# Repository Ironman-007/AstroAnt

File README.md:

# AstroAnt
Phase II of Rovables

The AstroAnt is the second generation of the Rovable project. The AstroAant also use magnetic wheels to attach to magnetic surface.

The AstroAnt is a modular design, and can carry different sensors to finish different kinds of diognostic missions, such as finding abnormal heating source, check CO2 leakage, detect metal flaw, and streaming video from remote.

Files descriptions:

- The 3D model of the robot is in the [Small_magnets_R821_with_gearbox](3dmodel/Small_magnets_R821_with_gearbox).

- The firmware of the robot is in [AstroAnt](Software/AstroAnt).

- The PC program (UI) is the [gui.py](Software/GUI_python/gui.py). Open with command line: ```python3 gui.py```

- The PCB design is in the [PCB](PCB). The [mainboard_v1](PCB/Mainboard/mainboard_v1/) is the design of the main control board, developed with KiCAD. The others are sensor modules design.

- The software of the central station for collecting data and distributing command is in [central_station](Software/Central_station/central_station/).

- The software of the central station for Camera in [cam_central](Software/Central_station/cam_central/).

- The Box design for the Zero-G flight test is in [Ant_Test_Box_DEC](3dmodel/Ant_Box_DEC/).

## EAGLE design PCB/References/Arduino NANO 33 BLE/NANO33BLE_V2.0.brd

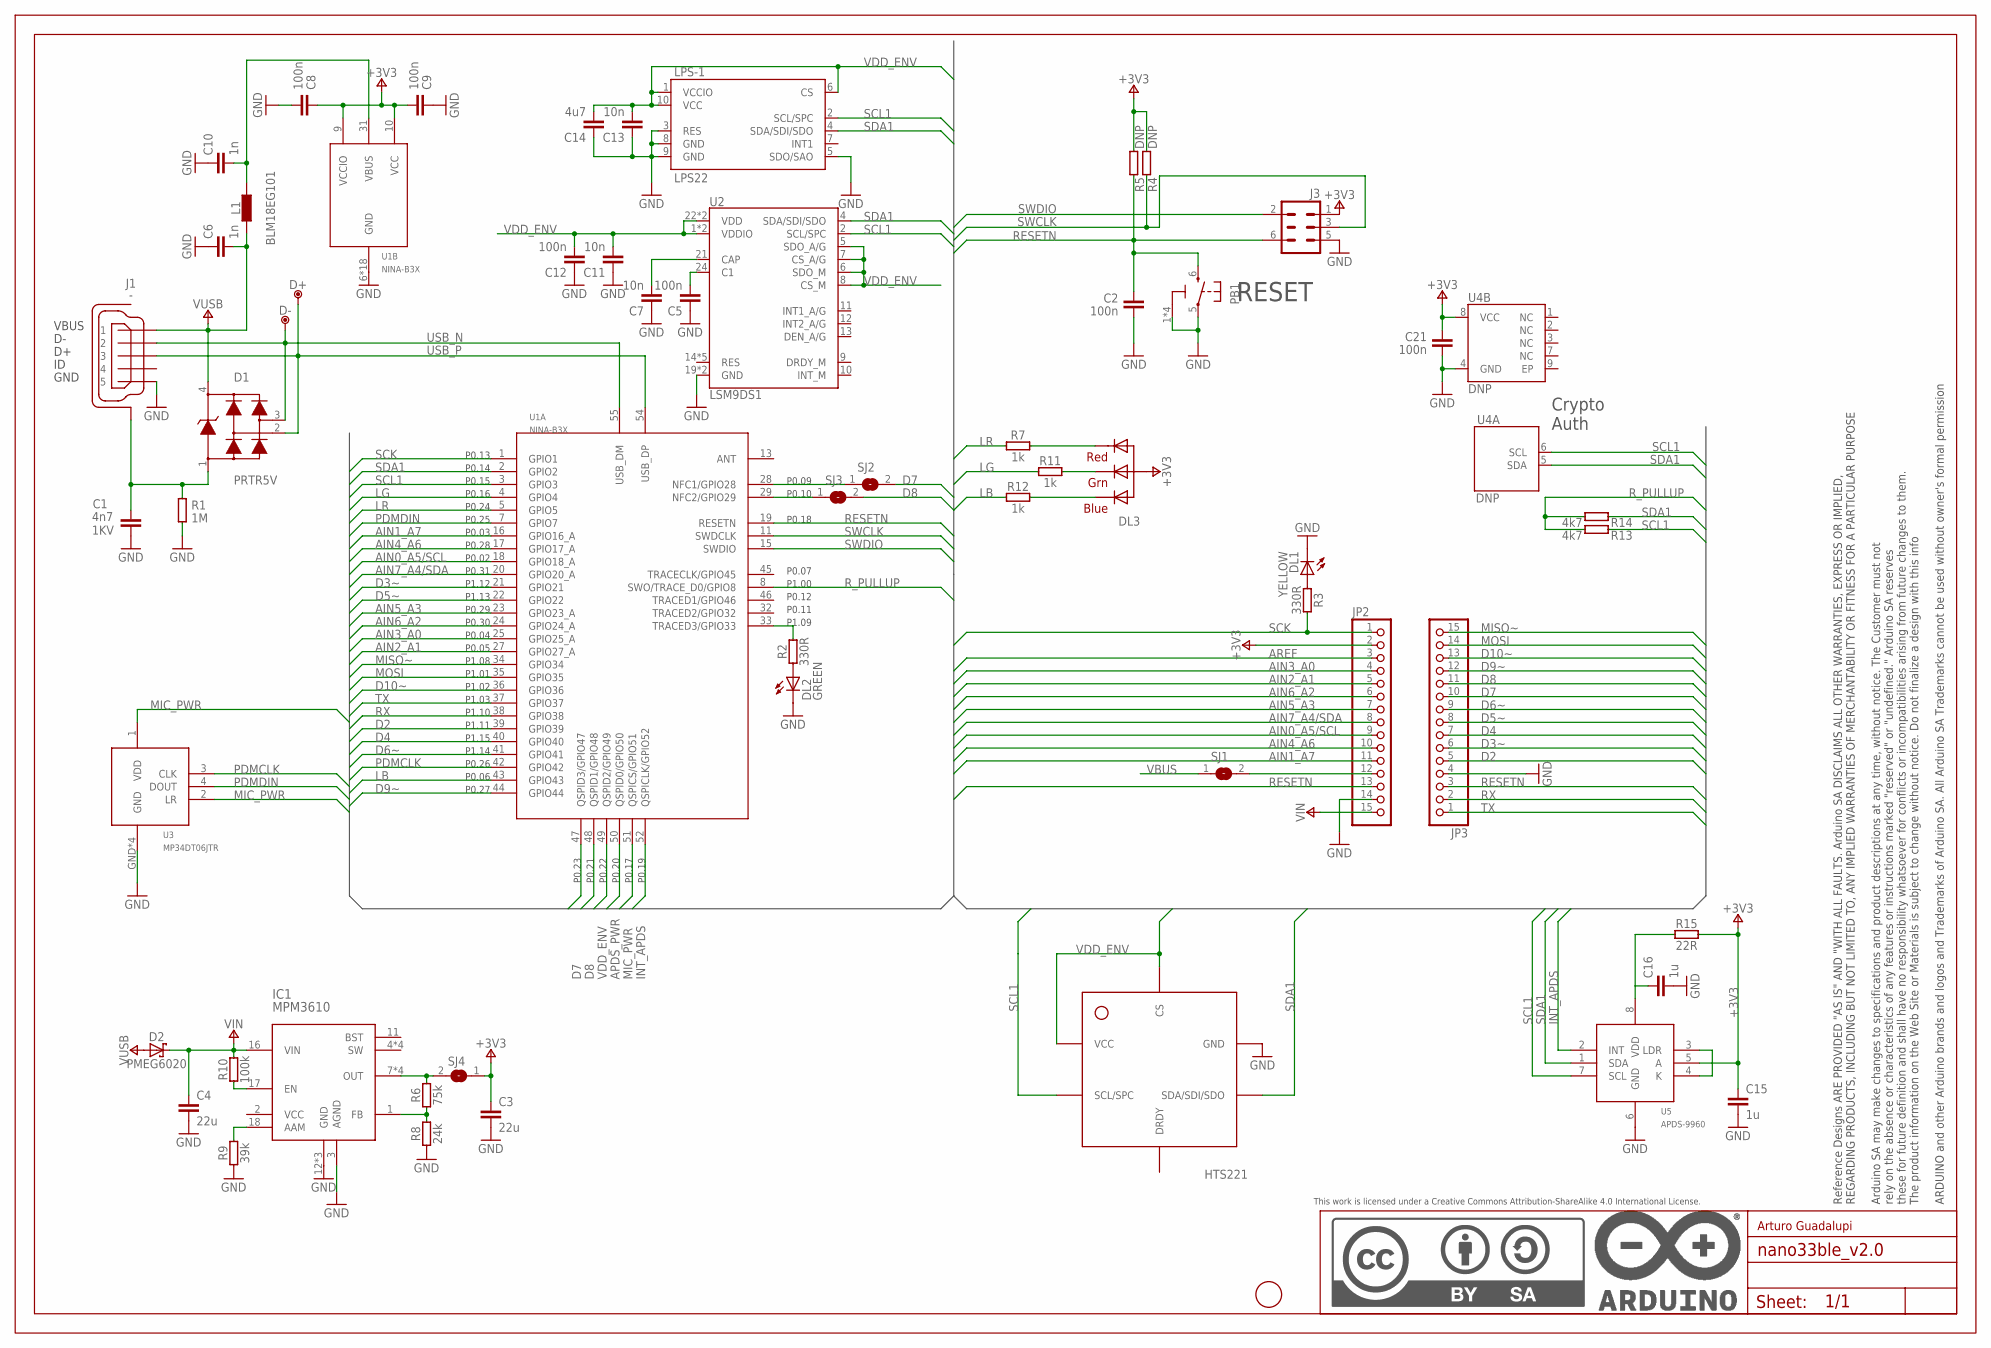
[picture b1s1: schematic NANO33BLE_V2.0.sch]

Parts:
C1: 4n7; 0805-R2013X50N; VOLTAGE 1KV
C2, C5, C8, C9, C12, C21: 100n; 0402-1005X55N
C3, C4: 22u; 0805-R2013X50N
C6, C10: 1n; 0402-1005X55N
C7, C11, C13: 10n; 0402-1005X55N
C14: 4u7; 0402-1005X55N
C15, C16: 1u; 0402-1005X55N
D1: PRTR5V; SOT190P230X110-4N
D2: PMEG6020; SODFL3517X110N
D+: DNP; TP-1.00MM
D-: DNP; TP-1.00MM
DL1: YELLOW; LEDC1608X80N-AK
DL2: GREEN; LEDC1608X80N-AK
DL3: -; SMLP34RGB2W
FD1: DNP; FD-1-1.5
FRAME1: DNP; FRAME
HS-1: HTS221
IC1: MPM3610
J1: -; ZX62-AB-5PA
J3: DNP; 2X03-TP1
JP2, JP3: PINHD-1X15-CASTELLATED; 1X15-CASTELL
L1: BLM18EG101; 0603-1608X90N
LPS-1: LPS22; LPS22H
PB1: PTS820; C&K_PTS820_NO_HOLES
R1: 1M; 0402-1005X55N
R2, R3: 330R; 0402-1005X55N
R4, R5: DNP; 0402-1005X55N
R6: 75k; 0402-1005X55N
R7, R11, R12: 1k; 0402-1005X55N
R8: 24k; 0402-1005X55N
R9: 39k; 0402-1005X55N
R10: 100k; 0402-1005X55N
R13, R14: 4k7; 0402-1005X55N
R15: 22R; 0402-1005X55N
SJ1, SJ2, SJ3, SJ4: DNP; SJ
U1: NINA-B3X
U2: LSM9DS1; LSM9DS1_TEMP_LGA24-8X4
U3: MP34DT06JTR; HCLGA
U4: DNP; SON50P300X200X60-9N-EP160X140
U5: APDS-9960; APDS9960

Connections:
+3V3: C3.1, C8.1, C9.2, C15.1, C21.1, DL3.1 (A), J3.1, JP2.2, R4.2, R5.2, R15.2, SJ4.1, U1.9 (VCCIO), U1.10 (VCC), U4.8 (VCC), U5.5 (A)
AIN0_A5/SCL: JP2.9, U1.18 (GPIO18_A)
AIN1_A7: JP2.11, U1.16 (GPIO16_A)
AIN2_A1: JP2.5, U1.27 (GPIO27_A)
AIN3_A0: JP2.4, U1.25 (GPIO25_A)
AIN4_A6: JP2.10, U1.17 (GPIO17_A)
AIN5_A3: JP2.7, U1.23 (GPIO23_A)
AIN6_A2: JP2.6, U1.24 (GPIO24_A)
AIN7_A4/SDA: JP2.8, U1.20 (GPIO20_A)
APDS_PWR: U1.50 (QSPID0/GPIO50)
AREF: JP2.3
D2: JP3.5, U1.39 (GPIO39)
D3~: JP3.6, U1.21 (GPIO21)
D4: JP3.7, U1.40 (GPIO40)
D5~: JP3.8, U1.22 (GPIO22)
D6~: JP3.9, U1.41 (GPIO41)
D7: JP3.10, SJ2.2, U1.47 (QSPID3/GPIO47)
D8: JP3.11, SJ3.2, U1.48 (QSPID1/GPIO48)
D9~: JP3.12, U1.44 (GPIO44)
D10~: JP3.13, U1.36 (GPIO36)
GND: C1.2, C2.2, C3.2, C4.2, C5.1, C6.1, C7.1, C8.2, C9.1, C10.1, C11.1, C12.1, C13.1, C14.1, C15.2, C16.2, C21.2, DL1.C, DL2.C, HS-1.P$5.GND (GND), IC1.3 (AGND), IC1.12 (GND), IC1.13 (GND), IC1.14 (GND), J1.5, J3.5, JP2.14, JP3.4, LPS-1.3 (RES), LPS-1.5 (SDO/SAO), LPS-1.8 (GND), LPS-1.9 (GND), PB1.1 (3), PB1.2 (3), PB1.3, PB1.4 (3), PB1.5 (1), R1.1, R8.1, R9.1, U1.6 (GND), U1.12 (GND), U1.14 (GND), U1.26 (GND), U1.30 (GND), U1.53 (GND), U1.GND@1 (GND), U1.GND@2 (GND), U1.GND@3 (GND), U1.GND@4 (GND), U1.GND@5 (GND), U1.GND@6 (GND), U1.GND@7 (GND), U1.GND@8 (GND), U1.GND@9 (GND), U1.GND@10 (GND), U1.GND@11 (GND), U1.GND@12 (GND), U2.19 (GND), U2.20 (GND), U3.GND, U3.GND@2 (GND), U3.GND@3 (GND), U3.GND@4 (GND), U4.4 (GND), U5.6 (GND)
INT_APDS: U1.52 (QSPICLK/GPIO52), U5.2 (INT)
LB: R12.1, U1.43 (GPIO43)
LG: R11.1, U1.4 (GPIO4)
LR: R7.1, U1.5 (GPIO5)
MIC_PWR: U1.51 (QSPICS/GPIO51), U3.1 (VDD), U3.2 (LR)
MISO~: JP3.15, U1.34 (GPIO34)
MOSI: JP3.14, U1.35 (GPIO35)
unnamed: C1.1, D1.1, J1.6 (SH), J1.7 (SH), J1.8 (SH), J1.9 (SH), J1.10 (SH), J1.11 (SH), R1.2
unnamed: DL2.A, R2.1
unnamed: DL1.A, R3.1
unnamed: C5.2, U2.24 (C1)
unnamed: IC1.1 (FB), R6.1, R8.2
unnamed: IC1.18 (AAM), R9.2
unnamed: IC1.17 (EN), R10.1
unnamed: C7.2, U2.21 (CAP)
unnamed: U5.3 (LDR), U5.4 (K)
unnamed: R2.2, U1.33 (TRACED3/GPIO33)
unnamed: DL3.3 (BLUE_C), R12.2
unnamed: DL3.2 (RED_C), R7.2
unnamed: DL3.4 (GREEN_C), R11.2
unnamed: JP2.12, SJ1.2
unnamed: C16.1, R15.1, U5.8 (VDD)
unnamed: IC1.7 (OUT), IC1.8 (OUT), IC1.9 (OUT), IC1.20 (OUT), R6.2, SJ4.2
NFC1: SJ2.1, U1.28 (NFC1/GPIO28)
NFC2: SJ3.1, U1.29 (NFC2/GPIO29)
PDMCLK: U1.42 (GPIO42), U3.3 (CLK)
PDMDIN: U1.7 (GPIO7), U3.4 (DOUT)
RESETN: C2.1, J3.6, JP2.13, JP3.3, PB1.6 (2), R5.1, U1.19 (RESETN)
RX: JP3.2, U1.38 (GPIO38)
R_PULLUP: R13.2, R14.2, U1.8 (SWO/TRACE_D0/GPIO8)
SCK: JP2.1, R3.2, U1.1 (GPIO1)
SCL1: HS-1.P$2.SCL/SPC (SCL/SPC), LPS-1.2 (SCL/SPC), R13.1, U1.3 (GPIO3), U2.2 (SCL/SPC), U4.6 (SCL), U5.7 (SCL)
SDA1: HS-1.P$4.SDA/SDI/SDO (SDA/SDI/SDO), LPS-1.4 (SDA/SDI/SDO), R14.1, U1.2 (GPIO2), U2.4 (SDA/SDI/SDO), U4.5 (SDA), U5.1 (SDA)
SWCLK: J3.3, R4.1, U1.11 (SWDCLK)
SWDIO: J3.2, U1.15 (SWDIO)
TX: JP3.1, U1.37 (GPIO37)
USB_N: D1.3, D-.X, J1.2, U1.55 (USB_DM)
USB_P: D1.2, D+.X, J1.3, U1.54 (USB_DP)
VBUS: C10.2, L1.2, SJ1.1, U1.31 (VBUS)
VDD_ENV: C11.2, C12.2, C13.2, C14.2, HS-1.P$1.VDD (VCC), HS-1.P$6.CS (CS), LPS-1.1 (VCCIO), LPS-1.6 (CS), LPS-1.10 (VCC), U1.49 (QSPID2/GPIO49), U2.1 (VDDIO), U2.3 (VDDIO), U2.5 (SDO_A/G), U2.6 (SDO_M), U2.7 (CS_A/G), U2.8 (CS_M), U2.22 (VDD), U2.23 (VDD)
VIN: C4.1, D2.C, IC1.16 (VIN), JP2.15, R10.2
VUSB: C6.2, D1.4, D2.A, J1.1, L1.1

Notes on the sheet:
RESET
Crypto Auth
Arturo Guadalupi
HTS221

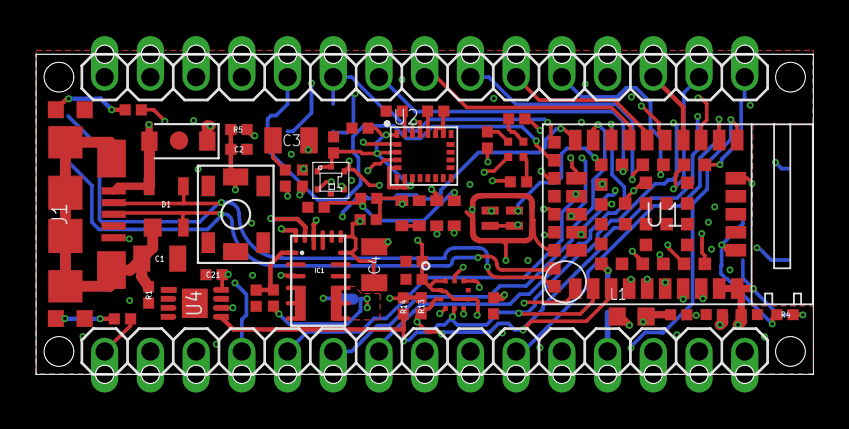
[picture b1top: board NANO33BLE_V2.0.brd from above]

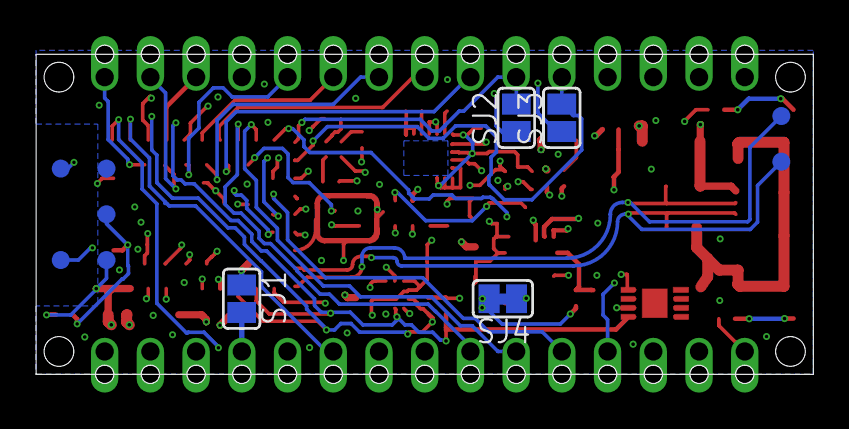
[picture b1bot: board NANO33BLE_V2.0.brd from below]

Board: 4 copper layers, 43.2 x 17.8 mm, 59 parts (4 on the bottom side), 61 nets.

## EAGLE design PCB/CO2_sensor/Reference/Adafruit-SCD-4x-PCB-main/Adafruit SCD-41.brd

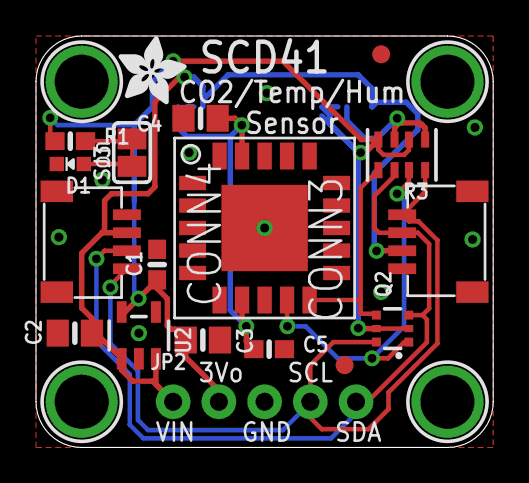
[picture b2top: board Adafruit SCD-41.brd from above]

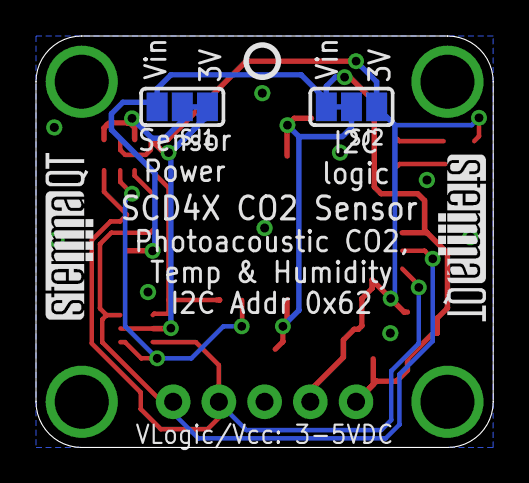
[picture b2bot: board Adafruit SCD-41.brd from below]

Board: 2 copper layers, 25.4 x 22.9 mm, 27 parts (5 on the bottom side), 11 nets.

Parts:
C1, C5: 0.1uF; 0603-NO
C2, C3, C4: 10uF; 0805-NO
CONN3, CONN4: STEMMA_I2C_QT; JST_SH4
D1: GREEN; CHIPLED_0603_NOOUTLINE
FID3, FID4: FIDUCIAL_1MM
JP2: 1X05_ROUND_76
Q2: BSS138; SOT363
R1: 10K; 0603-NO
R3: 10K; RESPACK_4X0603
SJ1, SJ2: SOLDERJUMPER_2WAY_OPEN_NOPASTE
SJ3: SOLDERJUMPER_CLOSEDWIRE
U2: AP2112K-3.3; SOT23-5
U$1, U$17, U$19, U$21: MOUNTINGHOLE3.0THIN; MOUNTINGHOLE_3.0_PLATEDTHIN
U$22: ADAFRUIT_3.5MM
U$25: PCBFEAT-REV-040
U$30, U$31: STEMMAQT
X1: SCD-41; SCD41

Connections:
3.3V: C1.1, C3.1, JP2.2, Q2.2, Q2.5, R1.1, R3.2, R3.4, SJ1.1, SJ2.1, U2.5
GND: C1.2, C2.2, C3.2, C4.2, C5.2, CONN3.1, CONN3.MT1, CONN3.MT2, CONN4.1, CONN4.MT1, CONN4.MT2, D1.C, JP2.3, U2.2, X1.6, X1.20, X1.P$1
unnamed: D1.A, SJ3.1
unnamed: R3.1, R3.3, SJ1.2
unnamed: C4.1, C5.1, SJ2.2, X1.7, X1.19
unnamed: R1.2, SJ3.2
SCL: CONN3.4, CONN4.4, JP2.4, Q2.6, R3.8
SCL_3V: Q2.1, R3.7, X1.9
SDA: CONN3.3, CONN4.3, JP2.5, Q2.3, R3.6
SDA_3V: Q2.4, R3.5, X1.10
VCC: C2.1, CONN3.2, CONN4.2, JP2.1, SJ1.3, SJ2.3, U2.1, U2.3

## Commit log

2021-08-02 udated by FZ
2021-11-13 updated by FZ

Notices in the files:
PCB/References/Arduino NANO 33 BLE/NANO33BLE_V2.0.brd:
Copyright (c) 2016-2017 Arduino LLC.  All right reserved. EAGLE Design Rules
parts and their libraries:
microbuilder: This work is placed in the public domain, and may be freely used for commercial and non-commercial work with the following conditions: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
Arduino-utility: This work is licensed under a Creative Commons Attribution-ShareAlike 4.0 International License.
